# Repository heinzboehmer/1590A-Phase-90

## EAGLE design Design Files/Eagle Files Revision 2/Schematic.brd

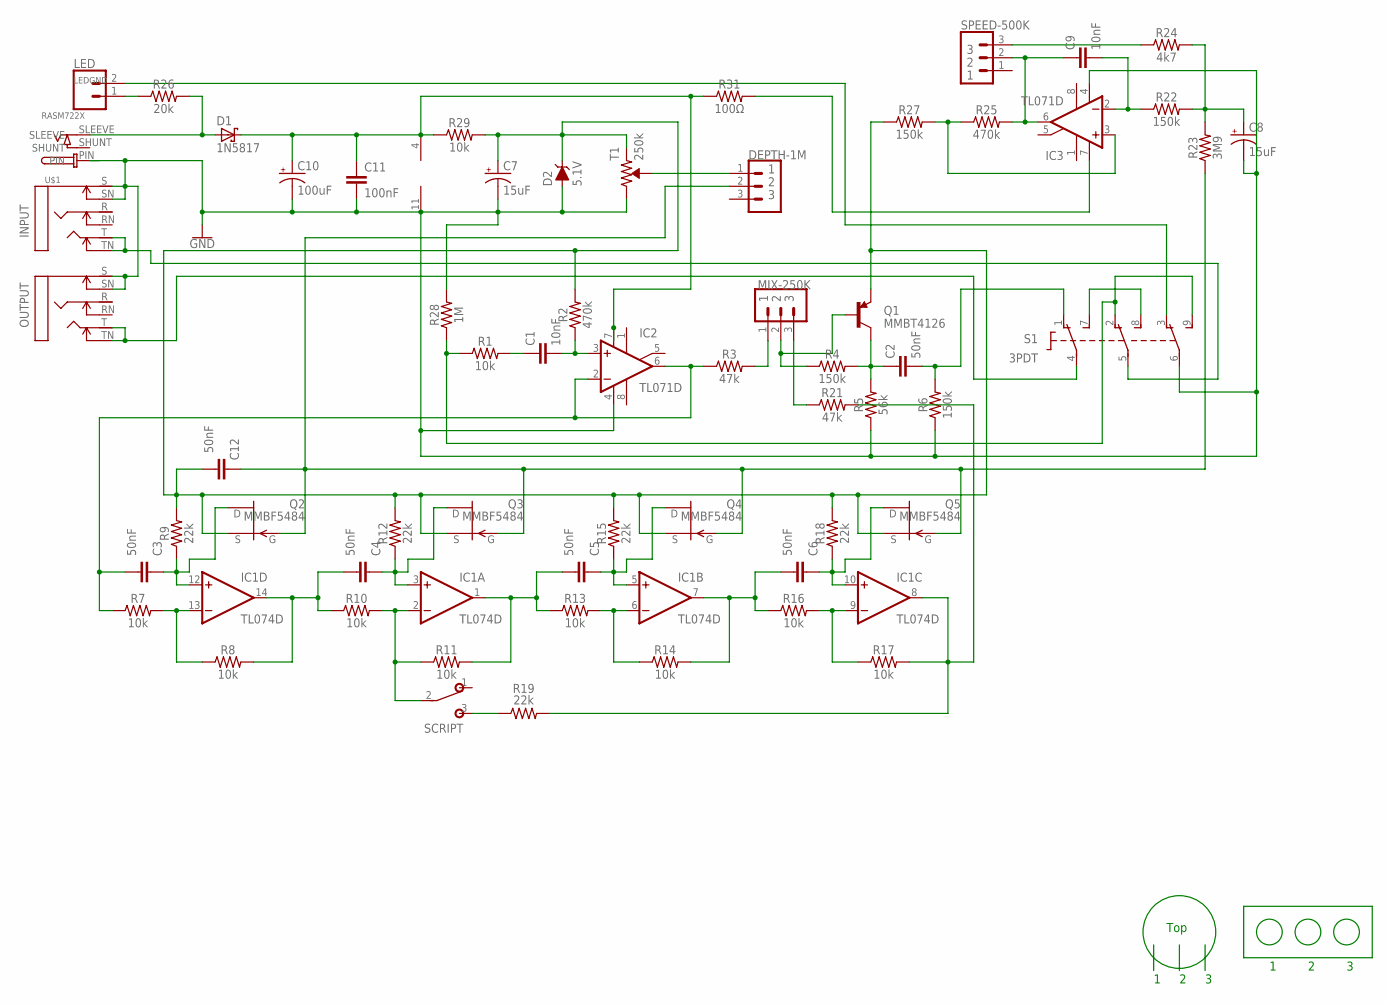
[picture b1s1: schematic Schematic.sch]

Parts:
C1, C9: 10nF; 0603
C2, C3, C4, C5, C6, C12: 50nF; 0603
C7, C8: 15uF; EIA7343
C10: 100uF; EIA7343
C11: 100nF; 0603
D1: 1N5817; DO41-7.6
D2: 5.1V; SOD-323
DEPTH-1M: CONN_03; 1X03
IC1: TL074D; SO14
IC2, IC3: TL071D; SO08
INPUT: STEREOSW; NMJ6HCD2
LED: CONN_02; 1X02
MIX-250K: CONN_03; 1X03
OUTPUT: STEREOSW; NMJ6HCD2
Q1: MMBT4126; SOT23-3
Q2, Q3, Q4, Q5: MMBF5484; SOT23
R1, R7, R8, R10, R11, R13, R14, R16, R17, R29: 10k; 0603
R2, R25: 470k; 0603
R3, R21: 47k; 0603
R4, R6, R22, R27: 150k; 0603
R5: 56k; 0603
R9, R12, R15, R18, R19: 22k; 0603
R23: 3M9; 0603
R24: 4k7; 0603
R26: 20k; 0603
R28: 1M; 0603
R31: 100Ω; 0603
S1: 3PDT
SCRIPT: SPDT; M9040P
SPEED-500K: CONN_03; 1X03
T1: 250k; TRIMPOT-SMD-3MM-CLOSED
U$1: RASM722X; SWITCHCRAFT_RASM722X

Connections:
1: MIX-250K.1, R3.2
2: C9.1, IC3.6 (OUT), R25.2, SPEED-500K.2
3: R24.1, SPEED-500K.3
4: C10.A (+), C11.1, D1.C, IC1.4 (V+), IC2.7 (V+), R29.1, R31.1
9V: D1.A, R26.2, U$1.SLEEVE
ASD: DEPTH-1M.1, T1.2 (WIPER)
GND: C7.C (-), C8.C (-), C10.C (-), C11.2, D2.A, IC1.11 (V-), IC2.4 (V-), IC3.4 (V-), INPUT.S, INPUT.SN, OUTPUT.S, OUTPUT.SN, R5.1, R6.1, R28.2, S1.6 (P3), T1.3 (CW), U$1.PIN
IN: INPUT.T, INPUT.TN, S1.5 (P2)
INN: R1.1, R28.1, S1.2 (O2), S1.9 (S3)
LEDGND: LED.2, S1.3 (O3)
unnamed: C4.2, IC1.14 (OUT), R8.2, R10.1
unnamed: IC1.13 (-IN), R7.2, R8.1
unnamed: C1.2, IC2.3 (+IN), R2.1
unnamed: C3.1, IC1.12 (+IN), Q2.1 (D), R9.1
unnamed: MIX-250K.3, R21.1
unnamed: C6.2, IC1.7 (OUT), R14.2, R16.1
unnamed: C5.2, IC1.1 (OUT), R11.2, R13.1
unnamed: R19.1, SCRIPT.3 (S)
unnamed: C4.1, IC1.3 (+IN), Q3.1 (D), R12.1
unnamed: LED.1, R26.1
unnamed: IC1.6 (-IN), R13.2, R14.1
unnamed: IC1.8 (OUT), R17.2, R19.2, R21.2
unnamed: C5.1, IC1.5 (+IN), Q4.1 (D), R15.1
unnamed: MIX-250K.2, Q1.1 (B), R4.1
unnamed: C1.1, R1.2
unnamed: IC1.9 (-IN), R16.2, R17.1
unnamed: C3.2, IC2.2 (-IN), IC2.6 (OUT), R3.1, R7.1
unnamed: C6.1, IC1.10 (+IN), Q5.1 (D), R18.1
unnamed: C12.1, DEPTH-1M.2, Q2.3 (G), Q3.3 (G), Q4.3 (G), Q5.3 (G), R23.1
unnamed: C2.1, Q1.3 (C), R4.2, R5.2
unnamed: IC3.7 (V+), R31.2
unnamed: C9.2, IC3.2 (-IN), R22.1
unnamed: C8.A (+), R22.2, R23.2, R24.2
unnamed: C7.A (+), C12.2, D2.C, Q1.2 (E), Q2.2 (S), Q3.2 (S), Q4.2 (S), Q5.2 (S), R2.2, R9.2, R12.2, R15.2, R18.2, R27.1, R29.2, T1.1 (CCW)
unnamed: C2.2, R6.2, S1.1 (O1)
unnamed: IC3.3 (+IN), R25.1, R27.2
unnamed: IC1.2 (-IN), R10.2, R11.1, SCRIPT.2
unnamed: S1.7 (S1), S1.8 (S2)
OUT: OUTPUT.T, OUTPUT.TN, S1.4 (P1)
SHUNT: U$1.SHUNT

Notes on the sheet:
Top

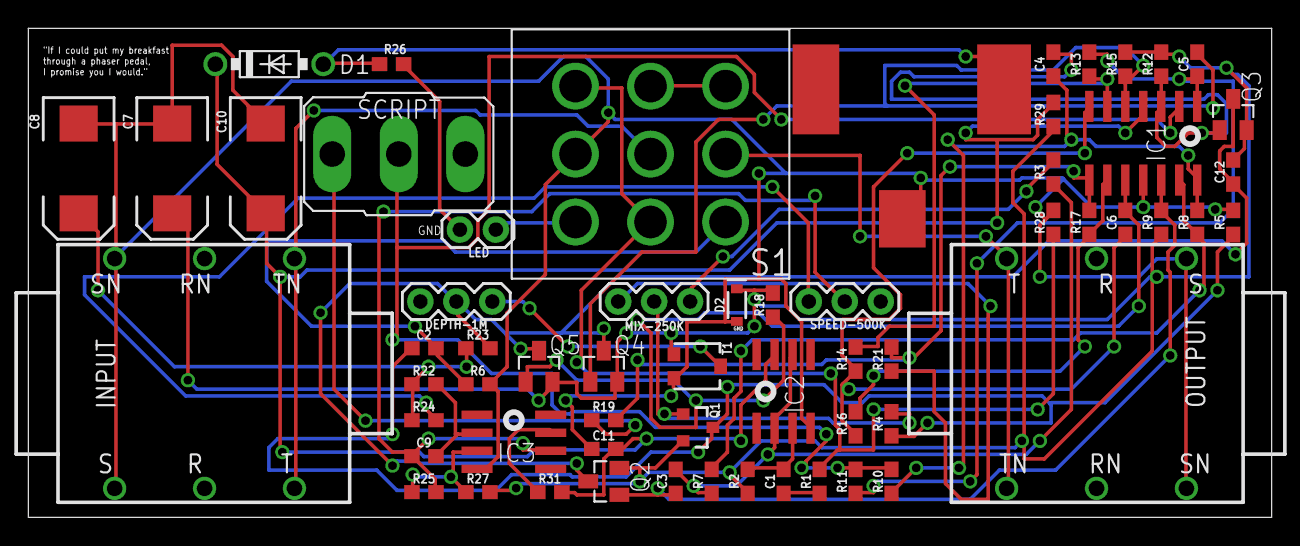
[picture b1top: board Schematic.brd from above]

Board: 2 copper layers, 87.8 x 34.5 mm, 61 parts (0 on the bottom side), 39 nets.

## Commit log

2017-02-21 Create afsd
2017-02-21 Create a
2017-02-21 Create d

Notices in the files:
parts and their libraries:
SparkFun-Capacitors: Licensing: Creative Commons ShareAlike 4.0 International - https://creativecommons.org/licenses/by-sa/4.0
